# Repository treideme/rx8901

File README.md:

# Seiko Epson RX8901CE Evaluation

This repository contains the sources for my blog post, [here](https://www.reidemeister.com/?p=565)

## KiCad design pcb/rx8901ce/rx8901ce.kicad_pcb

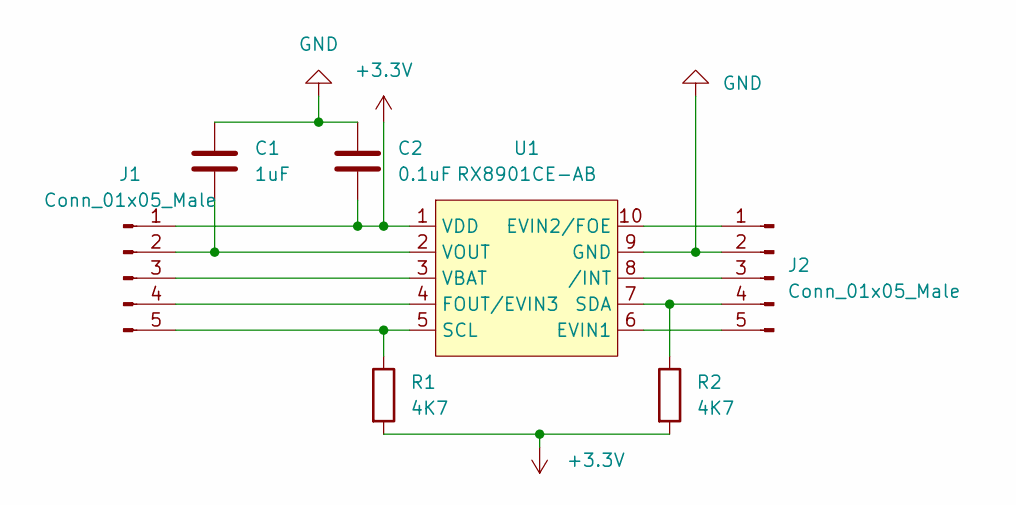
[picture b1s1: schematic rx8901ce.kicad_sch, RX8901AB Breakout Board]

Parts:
C1: 1uF; C_0603_1608Metric
C2: 0.1uF; C_0603_1608Metric
J1, J2: Conn_01x05_Male; PinHeader_1x05_P2.54mm_Vertical
R1, R2: 4K7; R_0603_1608Metric
U1: RX8901CE-AB; RX8901CE

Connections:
+3.3V: C2.2, J1.1, R1.2, R2.2, U1.1 (VDD)
GND: C1.1, C2.1, J2.2, U1.9 (GND)
unnamed: C1.2, J1.2, U1.2 (VOUT)
unnamed: J1.3, U1.3 (VBAT)
unnamed: J1.4, U1.4 (FOUT/EVIN3)
unnamed: J1.5, R1.1, U1.5 (SCL)
unnamed: J2.1, U1.10 (EVIN2/FOE)
unnamed: J2.3, U1.8 (/INT)
unnamed: J2.4, R2.1, U1.7 (SDA)
unnamed: J2.5, U1.6 (EVIN1)

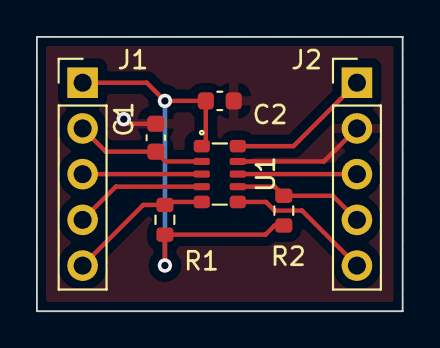
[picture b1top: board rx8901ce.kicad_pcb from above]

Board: 2 copper layers, 20.3 x 15.2 mm, 7 parts (0 on the bottom side), 10 nets.

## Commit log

2022-10-29 Basic library
2022-10-29 Working PCB
2022-10-30 PCB as ordered added Readme post blog
2022-11-20 WiP Driver
2022-11-21 Start of linux kernel module port
